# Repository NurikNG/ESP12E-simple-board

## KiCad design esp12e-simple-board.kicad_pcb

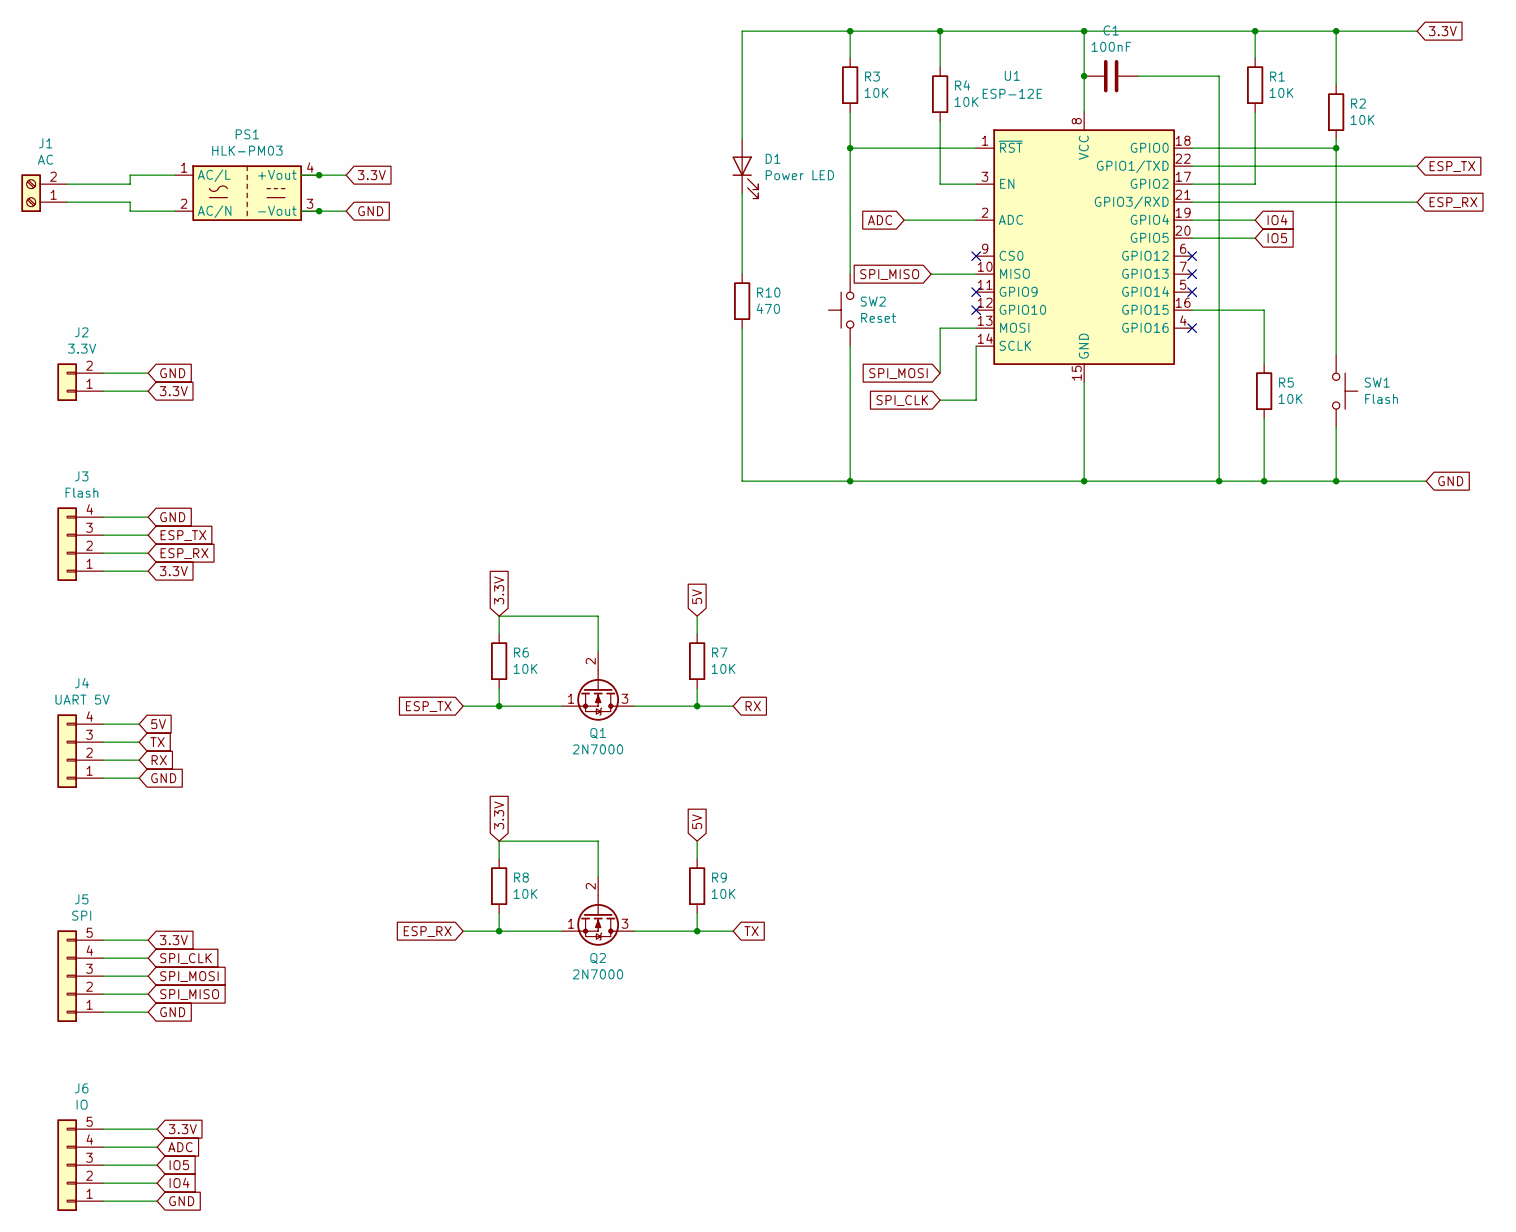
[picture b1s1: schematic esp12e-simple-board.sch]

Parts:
C1: 100nF; C_1206_3216Metric_Pad1.42x1.75mm_HandSolder
D1: Power LED; LED_1206_3216Metric_Pad1.42x1.75mm_HandSolder
J1: AC; TerminalBlock_Phoenix_MKDS-1,5-2_1x02_P5.00mm_Horizontal
J2: 3.3V; PinHeader_1x02_P2.54mm_Vertical
J3: Flash; PinHeader_1x04_P2.54mm_Vertical
J4: UART 5V; PinHeader_1x04_P2.54mm_Vertical
J5: SPI; PinHeader_1x05_P2.54mm_Vertical
J6: IO; PinHeader_1x05_P2.54mm_Vertical
PS1: HLK-PM03; Converter_ACDC_HiLink_HLK-PMxx
Q1, Q2: 2N7000; SOT-23_Handsoldering
R1, R2, R3, R4, R5, R6, R7, R8, R9: 10K; R_1206_3216Metric_Pad1.42x1.75mm_HandSolder
R10: 470; R_1206_3216Metric_Pad1.42x1.75mm_HandSolder
SW1: Flash; SW_PUSH_6mm_H13mm
SW2: Reset; SW_PUSH_6mm_H13mm
U1: ESP-12E

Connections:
3.3V: C1.2, D1.2 (A), J2.1, J3.1, J5.5, J6.5, PS1.4 (+Vout), Q1.2 (G), Q2.2 (G), R1.1, R2.1, R3.1, R4.1, R6.1, R8.1, U1.8 (VCC)
5V: J4.4, R7.1, R9.1
ADC: J6.4, U1.2 (ADC)
ESP_RX: J3.2, Q2.1 (S), R8.2, U1.21 (GPIO3/RXD)
ESP_TX: J3.3, Q1.1 (S), R6.2, U1.22 (GPIO1/TXD)
GND: C1.1, J2.2, J3.4, J4.1, J5.1, J6.1, PS1.3 (-Vout), R5.2, R10.2, SW1.2, SW2.1, U1.15 (GND)
IO4: J6.2, U1.19 (GPIO4)
IO5: J6.3, U1.20 (GPIO5)
unnamed: D1.1 (K), R10.1
unnamed: J1.1, PS1.2 (AC/N)
unnamed: J1.2, PS1.1 (AC/L)
unnamed: R1.2, U1.17 (GPIO2)
unnamed: R2.2, SW1.1, U1.18 (GPIO0)
unnamed: R3.2, SW2.2, U1.1 (~RST)
unnamed: R4.2, U1.3 (EN)
unnamed: R5.1, U1.16 (GPIO15)
RX: J4.2, Q1.3 (D), R7.2
SPI_CLK: J5.4, U1.14 (SCLK)
SPI_MISO: J5.2, U1.10 (MISO)
SPI_MOSI: J5.3, U1.13 (MOSI)
TX: J4.3, Q2.3 (D), R9.2

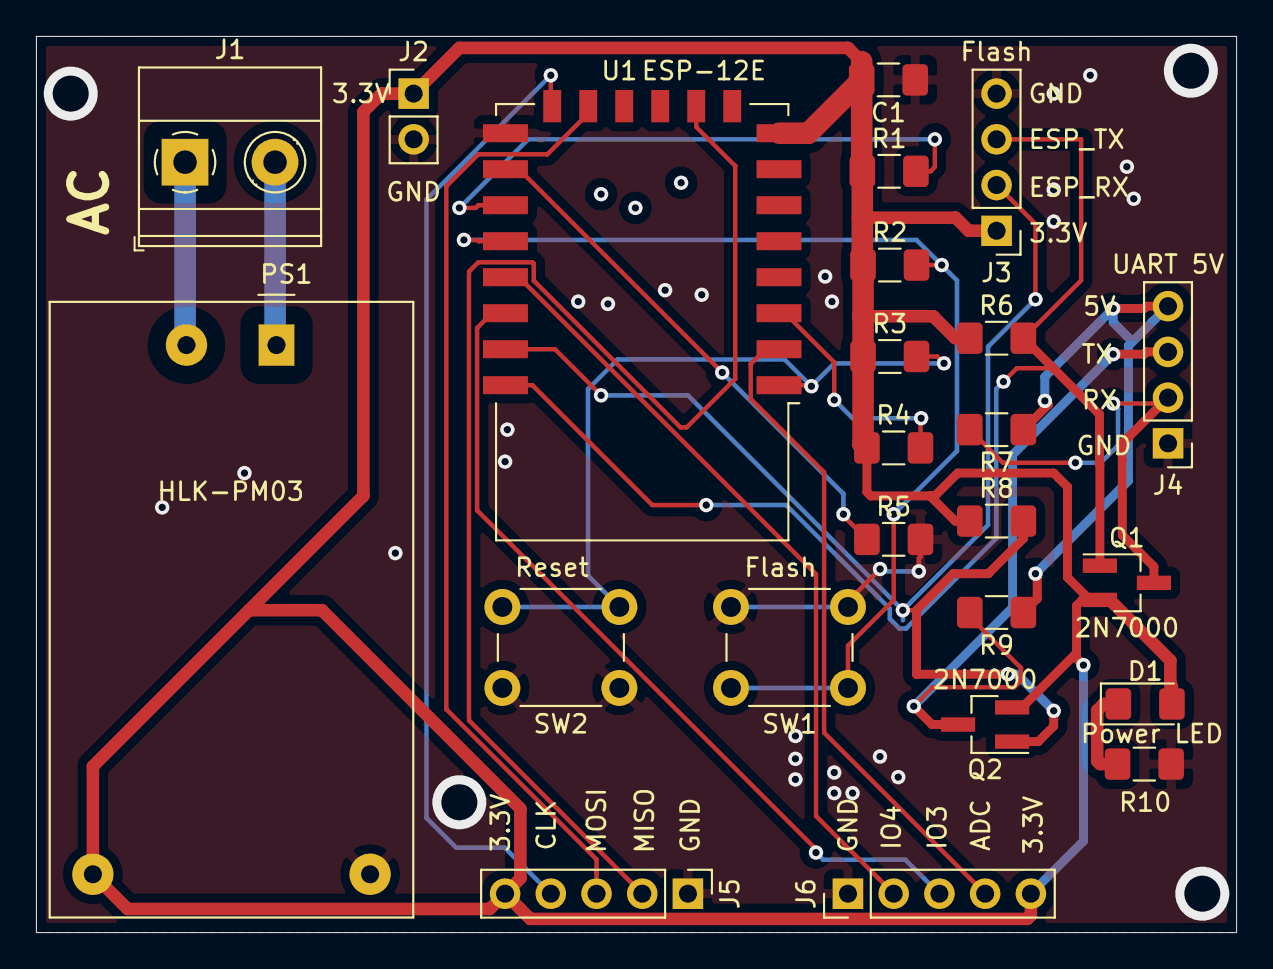
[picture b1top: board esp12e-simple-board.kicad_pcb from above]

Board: 2 copper layers, 66.7 x 49.8 mm, 24 parts (0 on the bottom side), 21 nets.

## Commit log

2019-12-24 Add files via upload
    v 0.1
2019-12-24 Add files via upload
    picture
